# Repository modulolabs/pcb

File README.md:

Modulo PCBs
===

This repository contains modulo circuit board schematics and pcb layouts.

Repository Contents
---

* Base/ - Eagle files for the Modulo Base
* Controller/ - Eagle files for the Modulo Controller
* Display/ - Eagle files for the Modulo Display
* Eagle/ - Common eagle files and libraries
* IRRemote/ - Eagle files for the Modulo IR Transceiver
* Joystick/ - Eagle files for the Modulo Joystick
* Knob/ - Eagle files for the Modulo Knob
* MotorDriver/ - Eagle files for Modulo Motor Driver
* Panel/ - Scripts for combining individual eagle boards into panels
* ParticleBase/ - Eagle files for the Modulo Particle Base
* Programmer/ - Eagle files for a board that's used to program other modulo boards
* TempProbe/ - Eagle files for the Modulo Temp Probe

Export
---

To export data for manufacturing:

* Load and run Eagle/Modulo.cam from the eagle cam processor. This will generate files in <Board>/Modulo<Board>RFQ/
* Run the ulp moundsmd.ulp and save the mount files to the same RFQ directory
* Run Eagle/integer-bom.ulp to generate the bom file and save it to the same RFQ directory.

License Information
-------------------
These circuit board designs are release under  [Creative Commons ShareAlike 4.0 International](https://creativecommons.org/licenses/by-sa/4.0/).

Please use, reuse, and modify these files as you see fit. Please maintain attribute to Modulo Labs LLC and release derivative work under the same license.

Distributed as-is; no warranty is given.

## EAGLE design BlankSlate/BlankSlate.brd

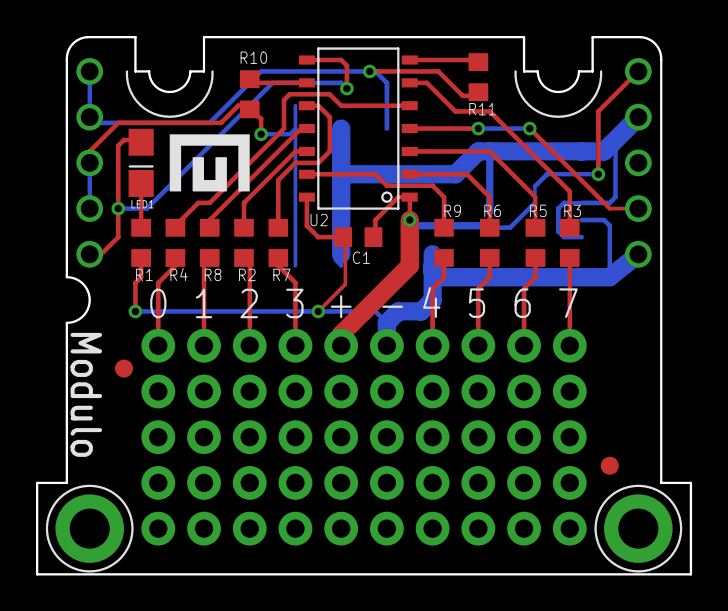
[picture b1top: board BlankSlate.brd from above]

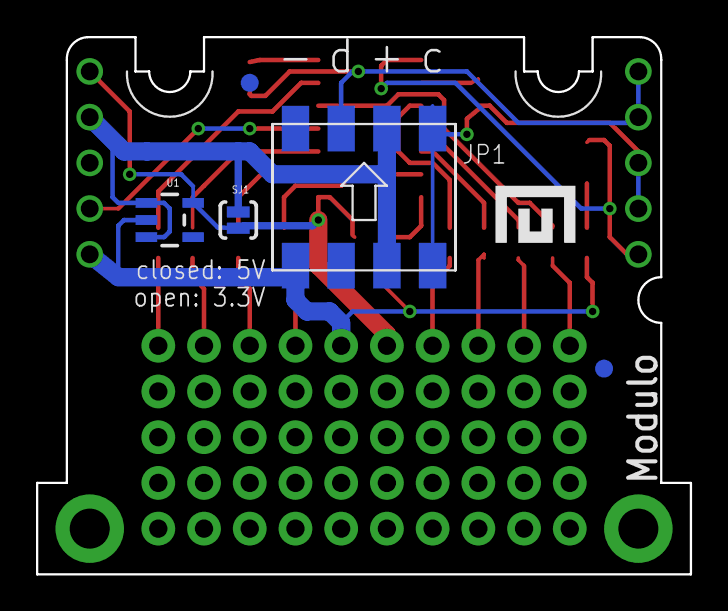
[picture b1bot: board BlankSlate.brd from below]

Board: 2 copper layers, 36.3 x 29.8 mm, 34 parts (16 on the bottom side), 26 nets.

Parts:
C1: .1uF; 0603
FID1, FID2, FID4, FID5: FIDUCIAL; FIDUCIAL_1MM
JP1: HEADER-1X4-AMPMODU; AMPMODU-4P
JP2, JP3, JP4, JP5, JP6, JP7, JP8, JP9, JP10, JP11: 1X05_NO_SILK
LED1: blue; 0805-LED
PCB1: DEVICE-PCB
R1: 1KΩ; 0603
R2, R3, R4, R5, R6, R7, R8, R9: 150Ω; 0603
R10, R11: 0Ω; 0603
SJ1: SOLDERJUMPERNO; SJ_2S-NO
U1: VREG-MIC5205-3.3V; SOT23-5
U2: ATTINY841; SOIC-14
U$1, U$2: LOGO-SMALL

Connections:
GND: C1.2, JP1.P$1, JP1.P$2, JP11.1, PCB1.GND, R1.1, U1.2, U2.14
IO0: R4.1, U2.5
IO1: R8.1, U2.11
IO2: R2.1, U2.12
IO3: R7.1, U2.10
IO4: R9.1, U2.13
IO5: R6.1, U2.2
IO6: R5.1, U2.3
IO7: R3.1, U2.6
MISO/LED: LED1.A, PCB1.MISO, U2.8
unnamed: JP4.1, R4.2
unnamed: JP5.1, R5.2
unnamed: JP7.1, R7.2
unnamed: JP2.1, R2.2
unnamed: JP3.1, R3.2
unnamed: JP6.1, R6.2
unnamed: JP9.1, R9.2
unnamed: LED1.C, R1.2
unnamed: JP8.1, R8.2
RESET: PCB1.RESET, U2.4
SCL: JP1.P$7, JP1.P$8, PCB1.CLK, PCB1.SCL, R10.1
SCL/SCK: R10.2, U2.9
SDA: JP1.P$3, JP1.P$4, PCB1.MOSI, PCB1.SDA, R11.1
SDA/MOSI: R11.2, U2.7
VCC: C1.1, JP10.1, PCB1.VPROG, SJ1.2, U1.5, U2.1
VIN: JP1.P$5, JP1.P$6, PCB1.VCC, SJ1.1, U1.1, U1.3

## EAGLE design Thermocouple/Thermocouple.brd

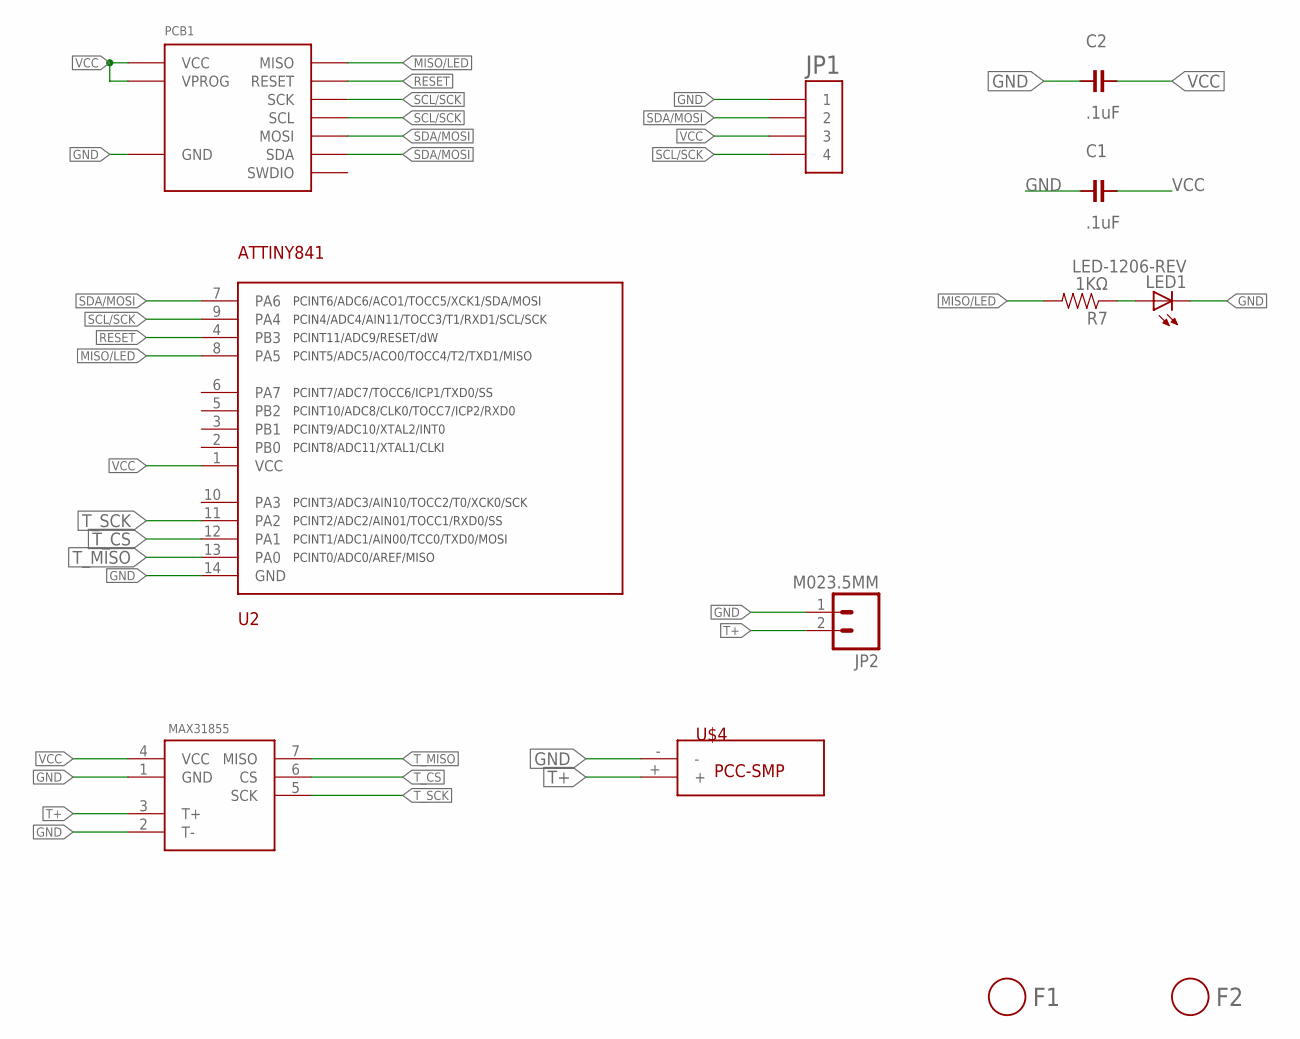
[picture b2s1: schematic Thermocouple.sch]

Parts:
C1, C2: .1uF; 0603
F1, F2: FIDUCIAL; FIDUCIAL_1MM
JP1: HEADER-1X4-AMPMODU; AMPMODU-4P
JP2: M023.5MM; SCREWTERMINAL-3.5MM-2
LED1: LED-1206-REV
PCB1: DEVICE-PCB; PARTNUM Therm PCB
R7: 1KΩ; 0603
U2: ATTINY841; SOIC-14
U$4: PCC-SMP
U$5: MAX31855; SOIC-8

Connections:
GND: C1.2, C2.2, JP1.P$1 (1), JP1.P$2 (1), JP2.1, LED1.C, PCB1.GND, U2.14 (GND), U$4.-, U$5.1 (GND), U$5.2 (T-)
MISO/LED: PCB1.MISO, R7.2, U2.8 (PA5)
unnamed: LED1.A, R7.1
RESET: PCB1.RESET, U2.4 (PB3)
SCL/SCK: JP1.P$7 (4), JP1.P$8 (4), PCB1.CLK (SCK), PCB1.SCL, U2.9 (PA4)
SDA/MOSI: JP1.P$3 (2), JP1.P$4 (2), PCB1.MOSI, PCB1.SDA, U2.7 (PA6)
T+: JP2.2, U$4.+, U$5.3 (T+)
T_CS: U2.12 (PA1), U$5.6 (CS)
T_MISO: U2.13 (PA0), U$5.7 (MISO)
T_SCK: U2.11 (PA2), U$5.5 (SCK)
VCC: C1.1, C2.1, JP1.P$5 (3), JP1.P$6 (3), PCB1.VCC, PCB1.VPROG, U2.1 (VCC), U$5.4 (VCC)

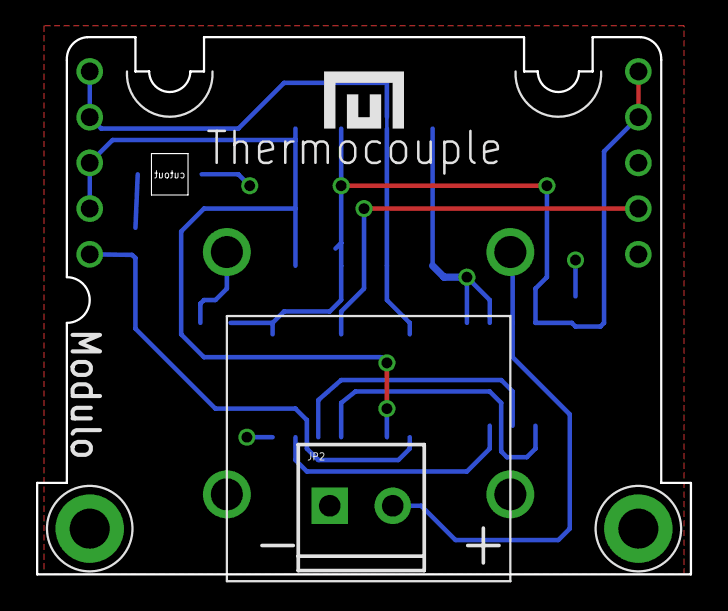
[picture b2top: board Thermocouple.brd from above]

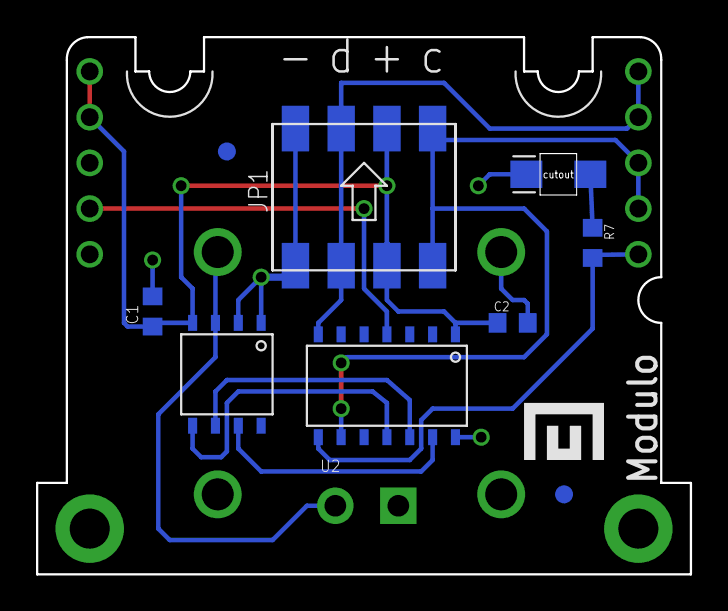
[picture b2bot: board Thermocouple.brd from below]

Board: 2 copper layers, 36.3 x 29.8 mm, 14 parts (10 on the bottom side), 11 nets.

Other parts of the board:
U$2, U$3: LOGO-SMALL

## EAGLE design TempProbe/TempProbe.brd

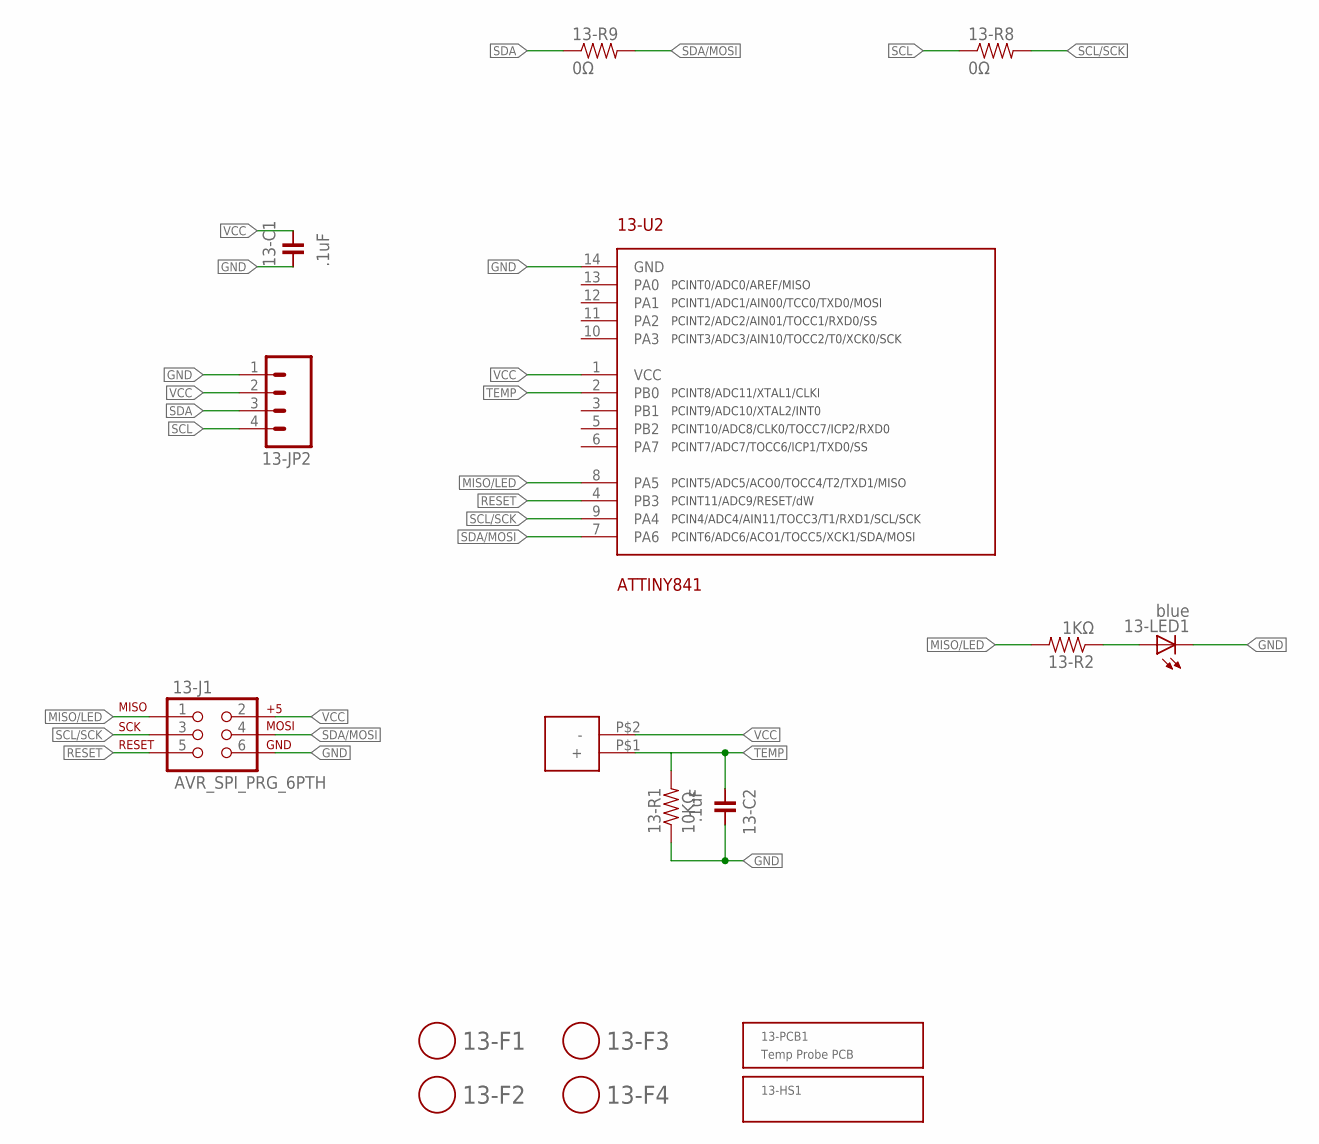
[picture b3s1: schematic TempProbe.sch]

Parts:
13-C1, 13-C2: .1uF; 0603
13-F1, 13-F2, 13-F3, 13-F4: FIDUCIAL; FIDUCIAL_1MM
13-J1: AVR_SPI_PRG_6PTH; 2X3
13-JP2: M041X04_NO_SILK; 1X04_NO_SILK
13-LED1: blue; 0805-LED
13-PROBE1: TEMP-PROBE; TEMP_PROBE; PARTNUM NTCLE413E2103F102L
13-R1: 10KΩ; 0603
13-R2: 1KΩ; 0603
13-R8, 13-R9: 0Ω; 0603
13-U2: ATTINY841; SOIC-14

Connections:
GND: 13-C1.2, 13-C2.1, 13-J1.6, 13-JP2.1, 13-LED1.C, 13-R1.1, 13-U2.14 (GND)
MISO/LED: 13-J1.1, 13-R2.2, 13-U2.8 (PA5)
unnamed: 13-LED1.A, 13-R2.1
RESET: 13-J1.5, 13-U2.4 (PB3)
SCL: 13-JP2.4, 13-R8.1
SCL/SCK: 13-J1.3, 13-R8.2, 13-U2.9 (PA4)
SDA: 13-JP2.3, 13-R9.1
SDA/MOSI: 13-J1.4, 13-R9.2, 13-U2.7 (PA6)
TEMP: 13-C2.2, 13-PROBE1.P$1 (+), 13-R1.2, 13-U2.2 (PB0)
VCC: 13-C1.1, 13-J1.2, 13-JP2.2, 13-PROBE1.P$2 (-), 13-U2.1 (VCC)

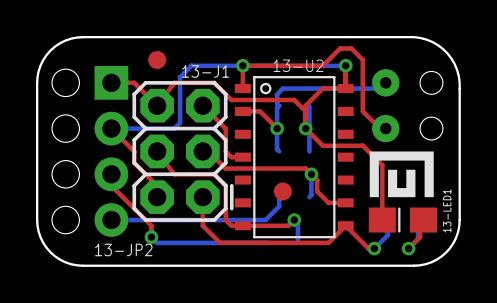
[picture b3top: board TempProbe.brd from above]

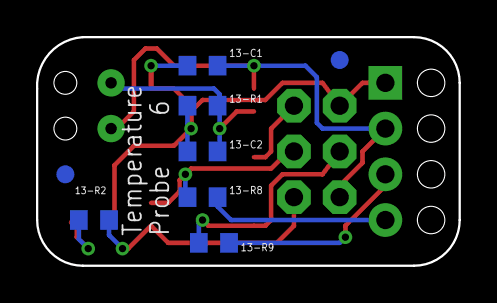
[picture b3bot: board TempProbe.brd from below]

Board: 2 copper layers, 23.5 x 12.7 mm, 16 parts (8 on the bottom side), 10 nets.

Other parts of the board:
U$1: LOGO-TINY

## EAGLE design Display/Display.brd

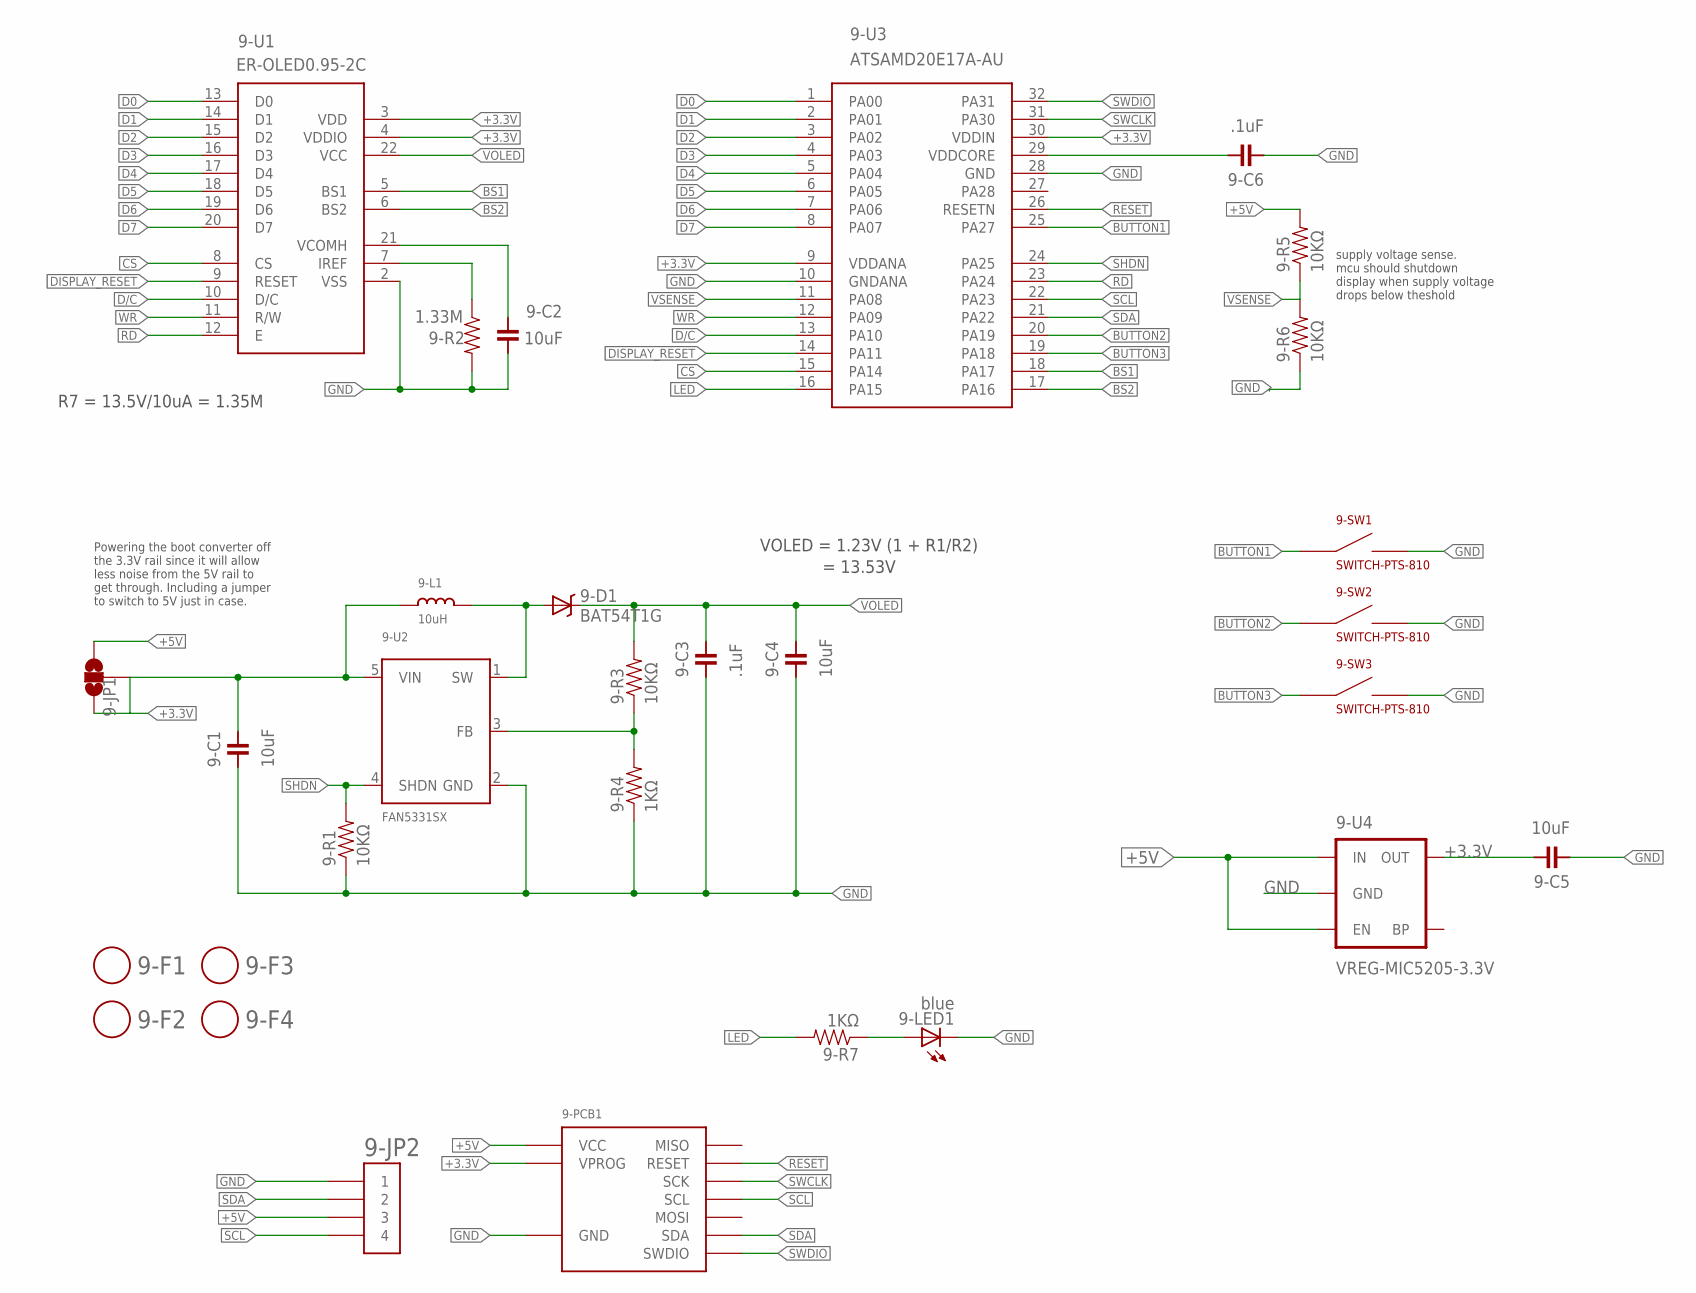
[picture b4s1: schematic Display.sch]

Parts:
9-C1, 9-C2, 9-C4, 9-C5: 10uF; 0603
9-C3, 9-C6: .1uF; 0603
9-D1: BAT54T1G; SMP
9-F1, 9-F2, 9-F3, 9-F4: FIDUCIAL; FIDUCIAL_1MM
9-JP1: SOLDERJUMPER_2WAYS; SJ_3
9-JP2: HEADER-1X4-AMPMODU; AMPMODU-4P
9-L1: 10uH; INDUCTOR_1007; PARTNUM MPI2520R1-100-R
9-LED1: blue; 0805-LED
9-PCB1: DEVICE-PCB; PARTNUM Display PCB
9-R1, 9-R3, 9-R5, 9-R6: 10KΩ; 0603
9-R2: 1.33M; 0603; PARTNUM ERJ-3EKF1304V
9-R4, 9-R7: 1KΩ; 0603
9-SW1, 9-SW2, 9-SW3: SWITCH-PTS-810; TACT-SWITCH-PTS-810
9-U1: ER-OLED0.95-2C; FPC-24-REVERSE; PARTNUM ER-OLED0.95-2C
9-U2: FAN5331SX; SOT23-5; PARTNUM FAN5331SX
9-U3: ATSAMD20E17A-AU; TQFP-32; PARTNUM ATSAMD20E17A-AU
9-U4: VREG-MIC5205-3.3V; SOT23-5; PARTNUM MIC5205-3.3YM5 TR

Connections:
+3.3V: 9-C1.1, 9-C5.1, 9-JP1.1, 9-JP1.2, 9-L1.P$1 (1), 9-PCB1.VPROG, 9-U1.3 (VDD), 9-U1.4 (VDDIO), 9-U2.5 (VIN), 9-U3.9 (VDDANA), 9-U3.30 (VDDIN), 9-U4.5 (OUT)
+5V: 9-JP1.3, 9-JP2.P$5 (3), 9-JP2.P$6 (3), 9-PCB1.VCC, 9-R5.2, 9-U4.1 (IN), 9-U4.3 (EN)
BS1: 9-U1.5 (BS1), 9-U3.18 (PA17)
BS2: 9-U1.6 (BS2), 9-U3.17 (PA16)
BUTTON1: 9-SW1.P$1 (POS1), 9-SW1.P$2 (POS1), 9-U3.25 (PA27)
BUTTON2: 9-SW2.P$1 (POS1), 9-SW2.P$2 (POS1), 9-U3.20 (PA19)
BUTTON3: 9-SW3.P$1 (POS1), 9-SW3.P$2 (POS1), 9-U3.19 (PA18)
CS: 9-U1.8 (CS), 9-U3.15 (PA14)
D0: 9-U1.13 (D0), 9-U3.1 (PA00)
D1: 9-U1.14 (D1), 9-U3.2 (PA01)
D2: 9-U1.15 (D2), 9-U3.3 (PA02)
D3: 9-U1.16 (D3), 9-U3.4 (PA03)
D4: 9-U1.17 (D4), 9-U3.5 (PA04)
D5: 9-U1.18 (D5), 9-U3.6 (PA05)
D6: 9-U1.19 (D6), 9-U3.7 (PA06)
D7: 9-U1.20 (D7), 9-U3.8 (PA07)
D/C: 9-U1.10 (D/C), 9-U3.13 (PA10)
DISPLAY_RESET: 9-U1.9 (RESET), 9-U3.14 (PA11)
GND: 9-C1.2, 9-C2.2, 9-C3.2, 9-C4.2, 9-C5.2, 9-C6.2, 9-JP2.P$1 (1), 9-JP2.P$2 (1), 9-LED1.C, 9-PCB1.GND, 9-R1.1, 9-R2.2, 9-R4.1, 9-R6.1, 9-SW1.P$3 (NEG1), 9-SW1.P$4 (NEG1), 9-SW2.P$3 (NEG1), 9-SW2.P$4 (NEG1), 9-SW3.P$3 (NEG1), 9-SW3.P$4 (NEG1), 9-U1.2 (VSS), 9-U2.2 (GND), 9-U3.10 (GNDANA), 9-U3.28 (GND), 9-U4.2 (GND)
LED: 9-R7.2, 9-U3.16 (PA15)
unnamed: 9-D1.A, 9-L1.P$2 (2), 9-U2.1 (SW)
unnamed: 9-R3.1, 9-R4.2, 9-U2.3 (FB)
unnamed: 9-C6.1, 9-U3.29 (VDDCORE)
unnamed: 9-C2.1, 9-U1.21 (VCOMH)
unnamed: 9-LED1.A, 9-R7.1
unnamed: 9-R2.1, 9-U1.7 (IREF)
RD: 9-U1.12 (E), 9-U3.23 (PA24)
RESET: 9-PCB1.RESET, 9-U3.26 (RESETN)
SCL: 9-JP2.P$7 (4), 9-JP2.P$8 (4), 9-PCB1.SCL, 9-U3.22 (PA23)
SDA: 9-JP2.P$3 (2), 9-JP2.P$4 (2), 9-PCB1.SDA, 9-U3.21 (PA22)
SHDN: 9-R1.2, 9-U2.4 (SHDN), 9-U3.24 (PA25)
SWCLK: 9-PCB1.CLK (SCK), 9-U3.31 (PA30)
SWDIO: 9-PCB1.SWDIO, 9-U3.32 (PA31)
VOLED: 9-C3.1, 9-C4.1, 9-D1.C, 9-R3.2, 9-U1.22 (VCC)
VSENSE: 9-R5.1, 9-R6.2, 9-U3.11 (PA08)
WR: 9-U1.11 (R/W), 9-U3.12 (PA09)

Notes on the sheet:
VOLED = 1.23V (1 + R1/R2)
= 13.53V
R7 = 13.5V/10uA = 1.35M
supply voltage sense. mcu should shutdown display when supply voltage drops below theshold
Powering the boot converter off the 3.3V rail since it will allow less noise from the 5V rail to get through. Including a jumper to switch to 5V just in case.

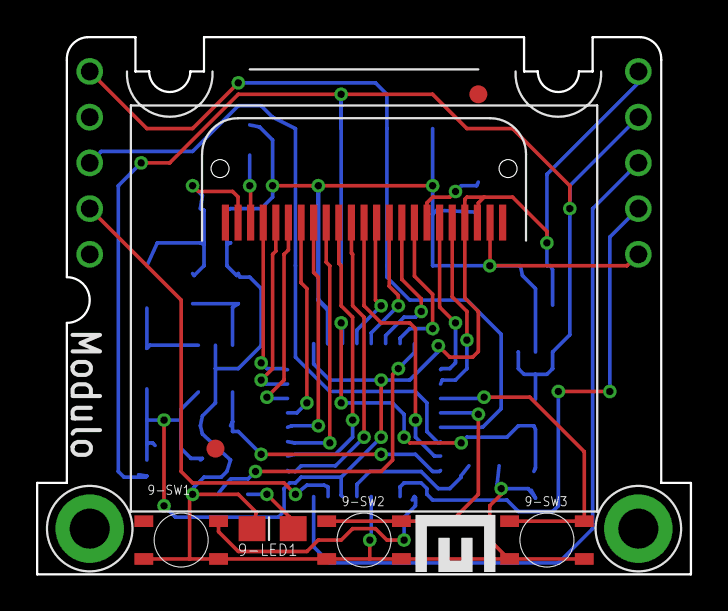
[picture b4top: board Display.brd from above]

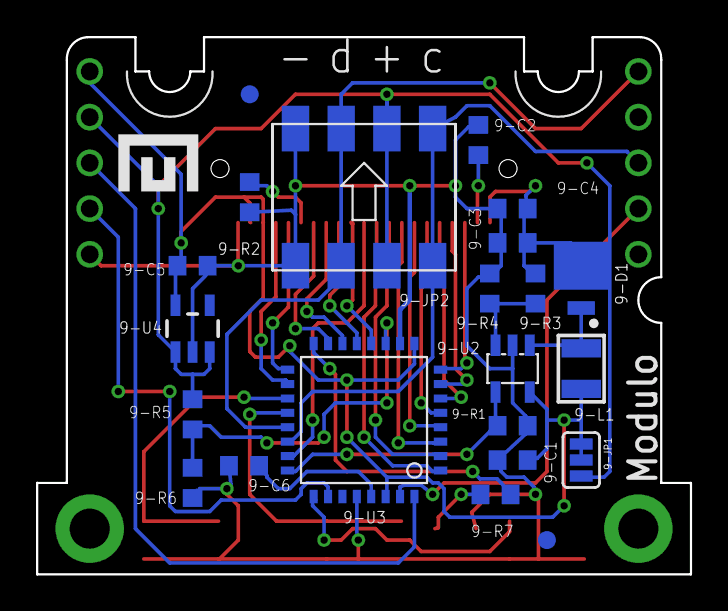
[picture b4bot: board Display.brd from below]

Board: 2 copper layers, 36.3 x 29.8 mm, 32 parts (23 on the bottom side), 36 nets.

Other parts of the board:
U$1, U$2: LOGO-SMALL

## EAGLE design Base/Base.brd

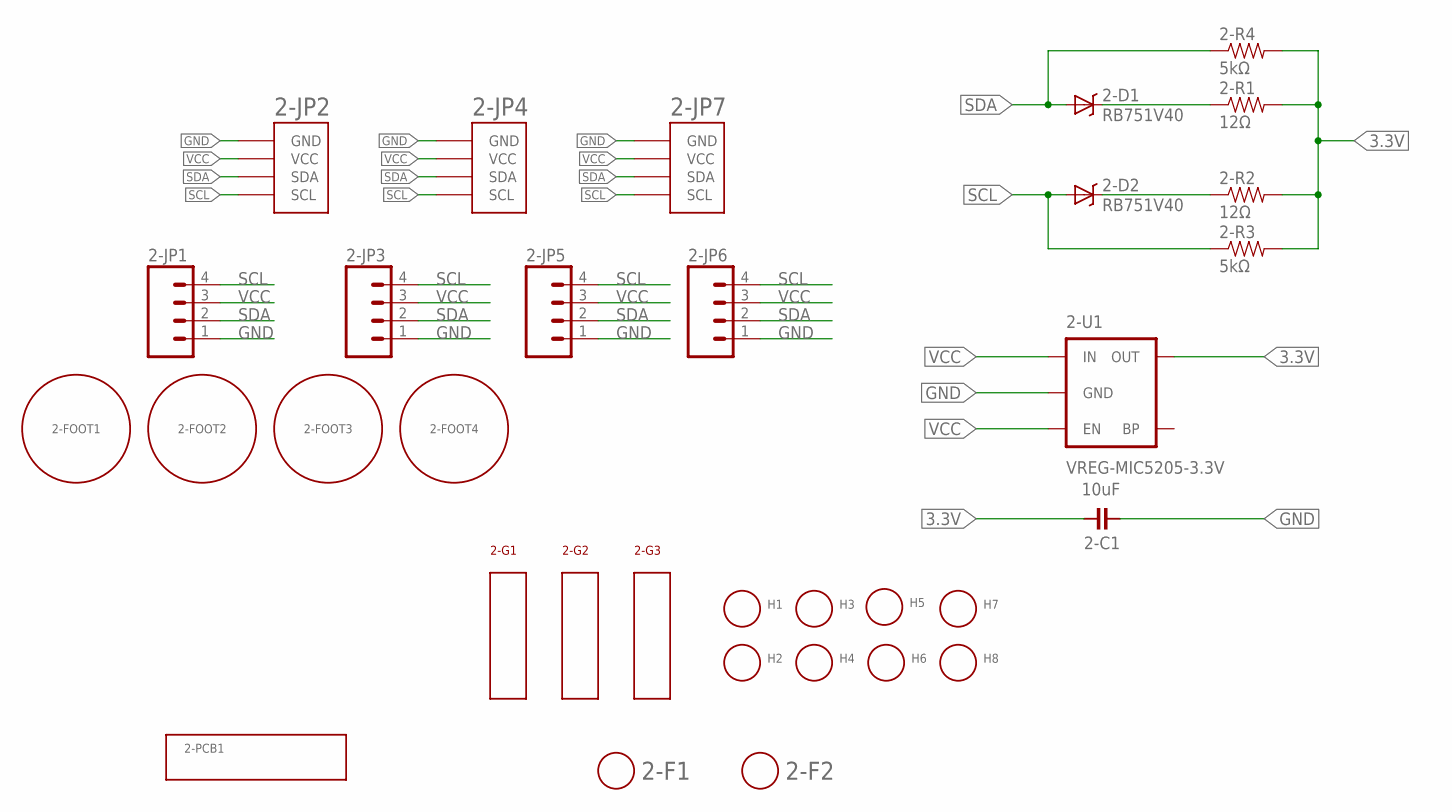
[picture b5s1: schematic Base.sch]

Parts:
2-C1: 10uF; 0603
2-D1, 2-D2: RB751V40; SOD-323; PARTNUM RB751V40
2-F1, 2-F2: FIDUCIAL; FIDUCIAL_1MM
2-FOOT1, 2-FOOT2, 2-FOOT3, 2-FOOT4: FOOT
2-G1, 2-G3: CARD-GUIDE; CARD-GUIDE-2; PARTNUM HCG-201-165
2-G2: CARD-GUIDE; CARD-GUIDE-2; PARTNUM HCG-202-165
2-JP1, 2-JP3, 2-JP5, 2-JP6: M04LOCK; 1X04_LOCK; PARTNUM M20-9750446
2-JP2, 2-JP4, 2-JP7: HEADER-MODULO; JST-PA-SIDE-SMD
2-R1, 2-R2: 12Ω; 0603
2-R3, 2-R4: 5kΩ; 0603
2-U1: VREG-MIC5205-3.3V; SOT23-5
H1, H2, H3, H4, H5, H6, H7, H8: HOLE#2; HOLE-#2

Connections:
3.3V: 2-C1.1, 2-R1.2, 2-R2.2, 2-R3.2, 2-R4.2, 2-U1.5 (OUT)
GND: 2-C1.2, 2-JP1.1, 2-JP2.1 (GND), 2-JP3.1, 2-JP4.1 (GND), 2-JP5.1, 2-JP6.1, 2-JP7.1 (GND), 2-U1.2 (GND)
unnamed: 2-D2.C, 2-R2.1
unnamed: 2-D1.C, 2-R1.1
SCL: 2-D2.A, 2-JP1.4, 2-JP2.4 (SCL), 2-JP3.4, 2-JP4.4 (SCL), 2-JP5.4, 2-JP6.4, 2-JP7.4 (SCL), 2-R3.1
SDA: 2-D1.A, 2-JP1.2, 2-JP2.3 (SDA), 2-JP3.2, 2-JP4.3 (SDA), 2-JP5.2, 2-JP6.2, 2-JP7.3 (SDA), 2-R4.1
VCC: 2-JP1.3, 2-JP2.2 (VCC), 2-JP3.3, 2-JP4.2 (VCC), 2-JP5.3, 2-JP6.3, 2-JP7.2 (VCC), 2-U1.1 (IN), 2-U1.3 (EN)

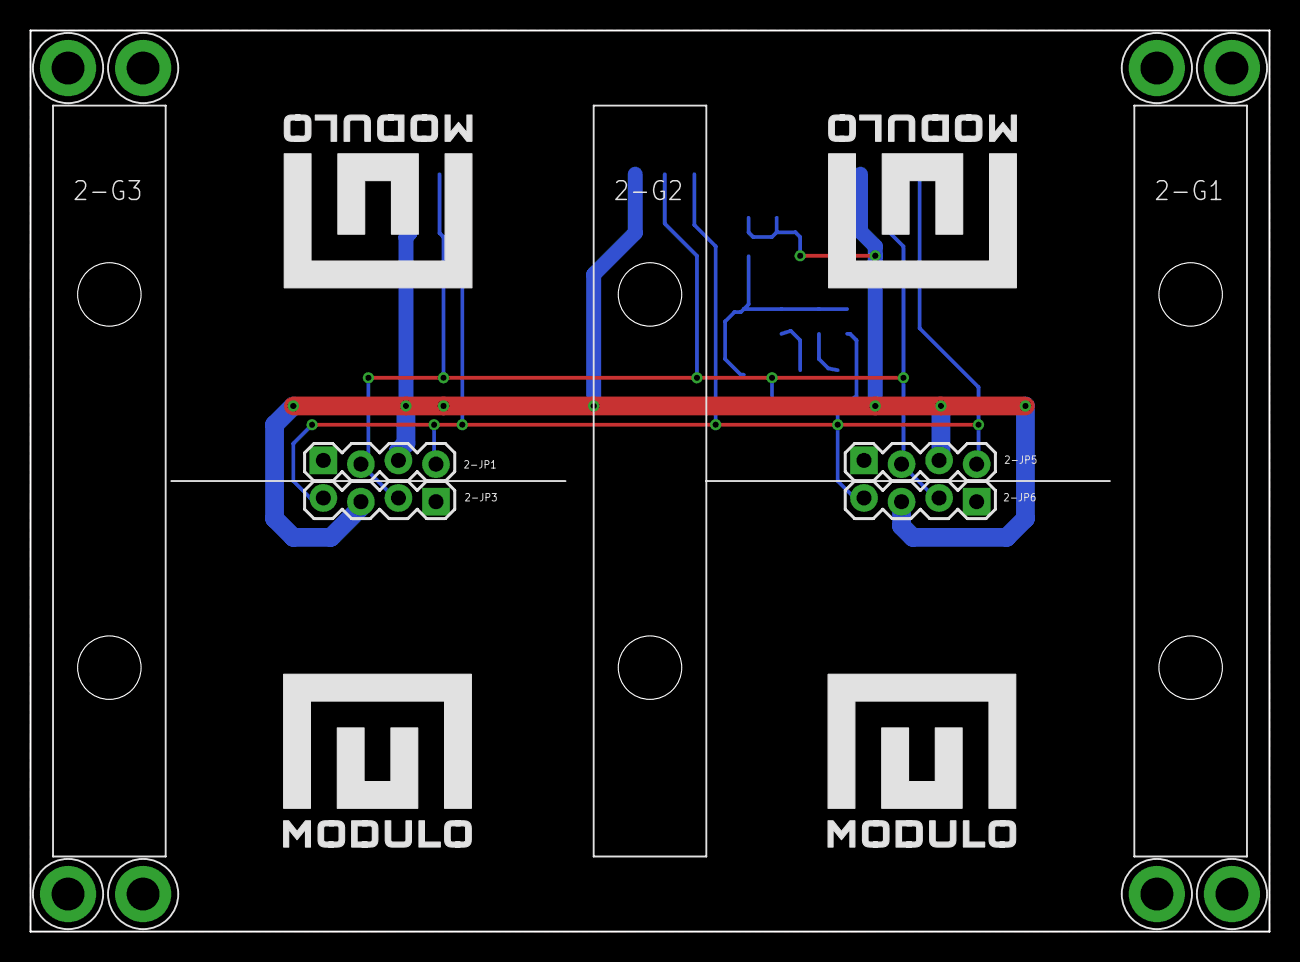
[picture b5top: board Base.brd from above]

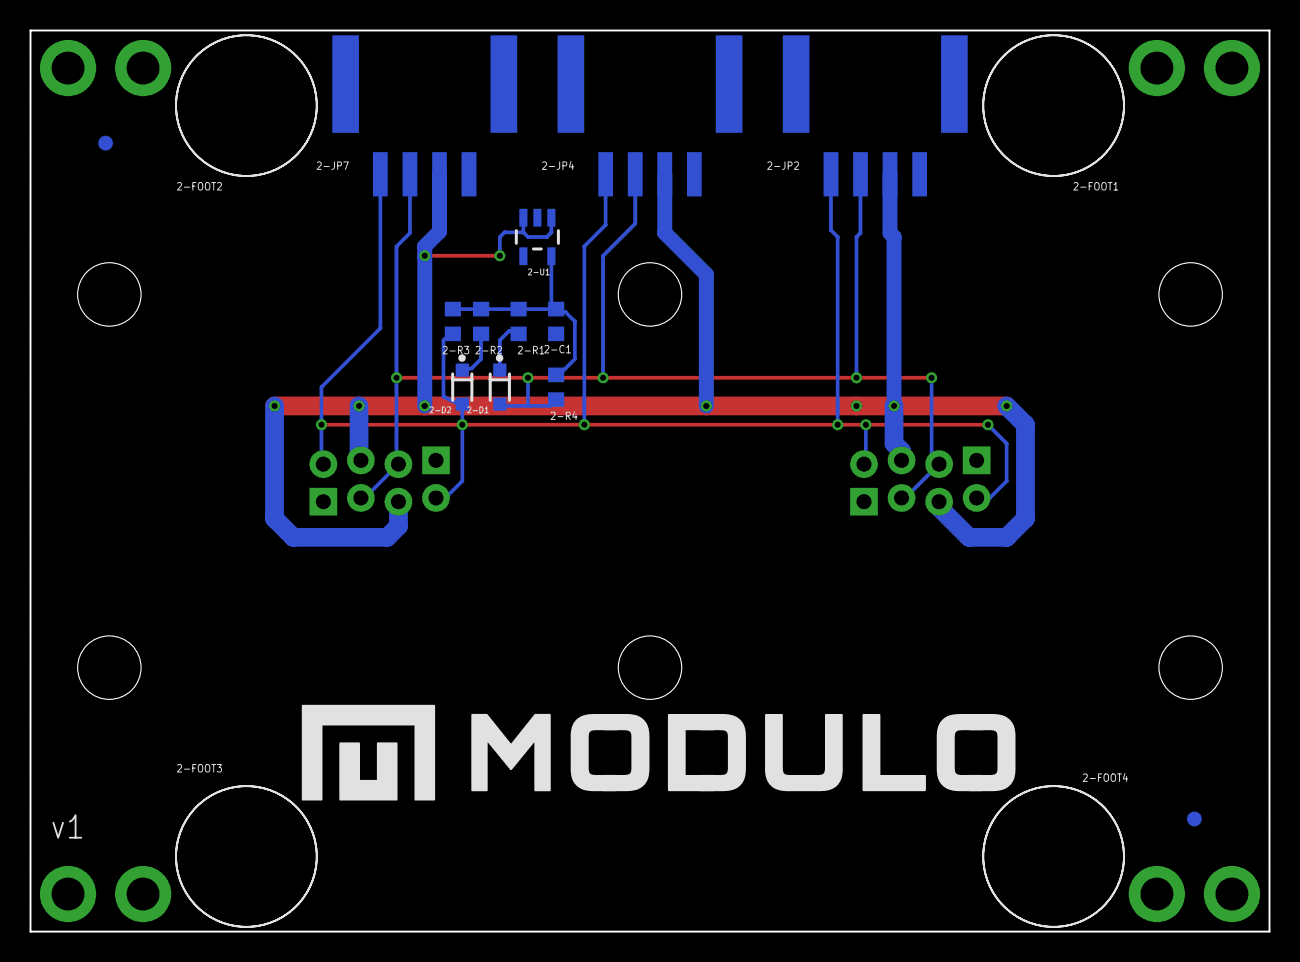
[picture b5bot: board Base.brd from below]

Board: 2 copper layers, 83.8 x 61.0 mm, 37 parts (18 on the bottom side), 7 nets.

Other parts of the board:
U$1: LOGO-HOR-0.25
U$3, U$4, U$5, U$6: LOGO-0.5

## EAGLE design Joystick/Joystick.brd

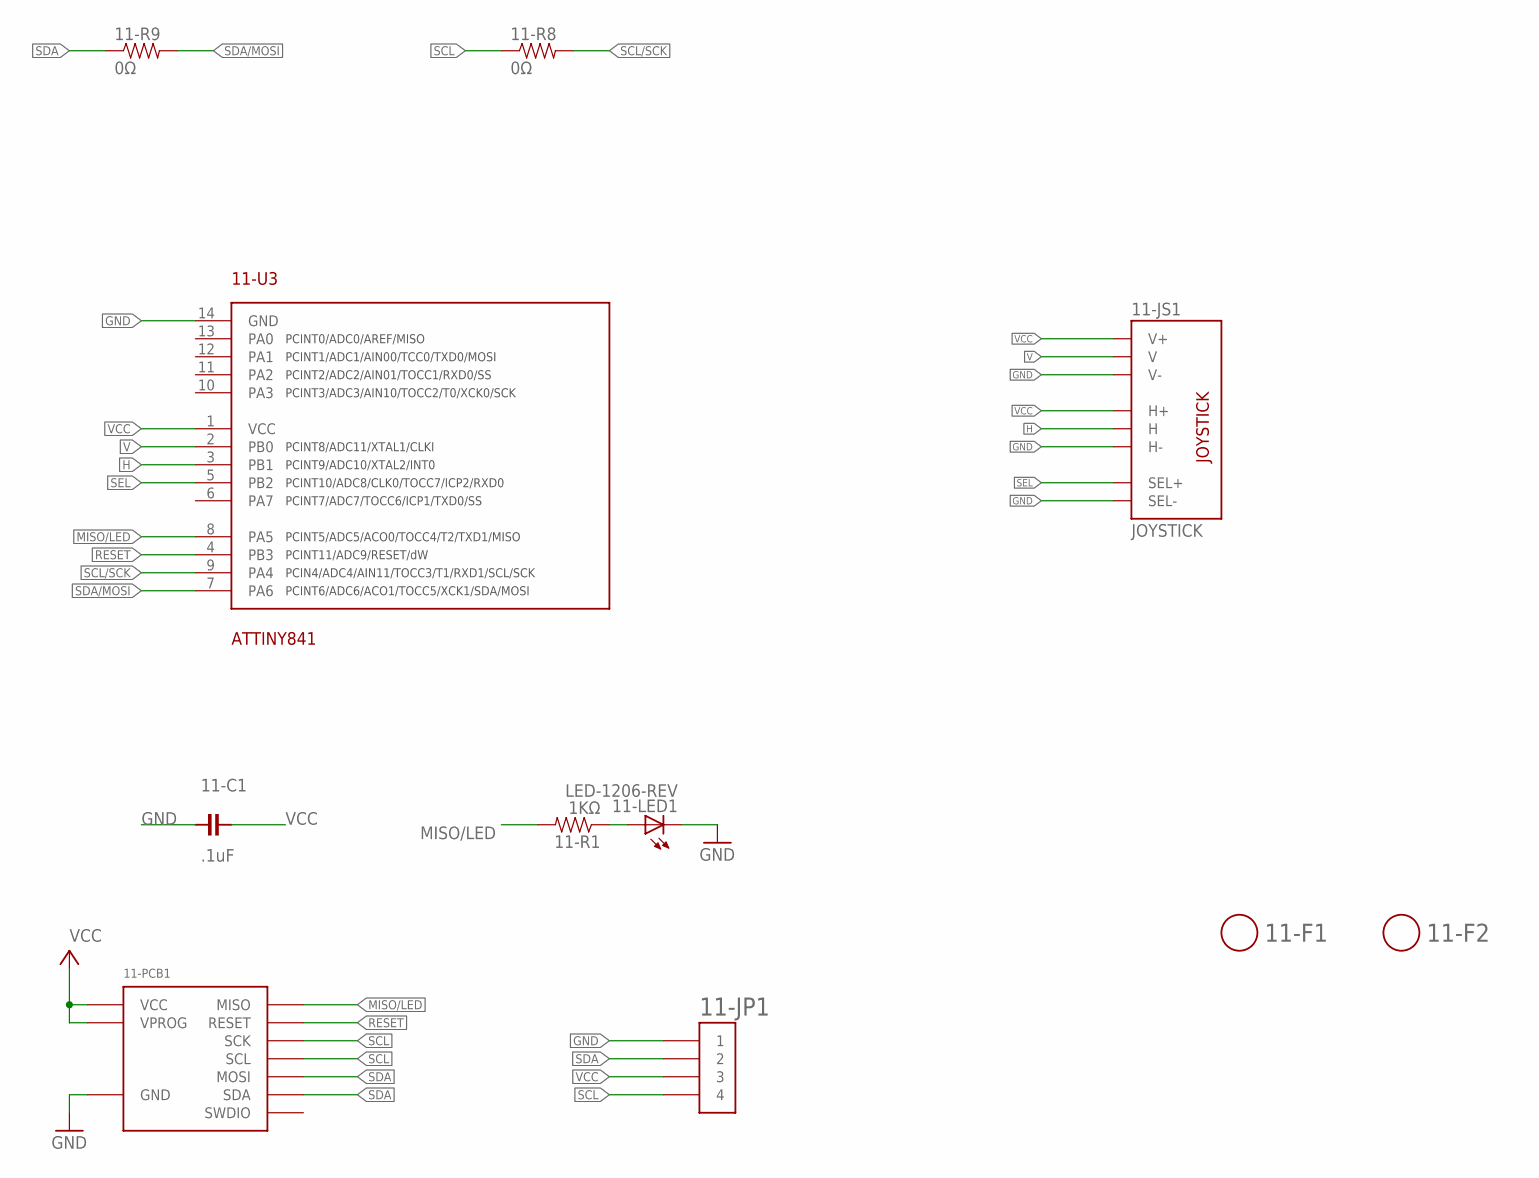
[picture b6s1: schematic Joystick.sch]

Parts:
11-C1: .1uF; 0603
11-F1, 11-F2: FIDUCIAL; FIDUCIAL_1MM
11-JP1: HEADER-1X4-AMPMODU; AMPMODU-4P
11-JS1: JOYSTICK; PARTNUM Joystick
11-LED1: LED-1206-REV
11-PCB1: DEVICE-PCB; PARTNUM Joystick PCB
11-R1: 1KΩ; 0603
11-R8, 11-R9: 0Ω; 0603
11-U3: ATTINY841; SOIC-14

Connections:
GND: 11-C1.2, 11-JP1.P$1 (1), 11-JP1.P$2 (1), 11-JS1.B2A (SEL-), 11-JS1.H3 (H-), 11-JS1.V3 (V-), 11-LED1.C, 11-PCB1.GND, 11-U3.14 (GND)
H: 11-JS1.H2 (H), 11-U3.3 (PB1)
MISO/LED: 11-PCB1.MISO, 11-R1.2, 11-U3.8 (PA5)
unnamed: 11-LED1.A, 11-R1.1
RESET: 11-PCB1.RESET, 11-U3.4 (PB3)
SCL: 11-JP1.P$7 (4), 11-JP1.P$8 (4), 11-PCB1.CLK (SCK), 11-PCB1.SCL, 11-R8.1
SCL/SCK: 11-R8.2, 11-U3.9 (PA4)
SDA: 11-JP1.P$3 (2), 11-JP1.P$4 (2), 11-PCB1.MOSI, 11-PCB1.SDA, 11-R9.1
SDA/MOSI: 11-R9.2, 11-U3.7 (PA6)
SEL: 11-JS1.B1A (SEL+), 11-U3.5 (PB2)
V: 11-JS1.V2 (V), 11-U3.2 (PB0)
VCC: 11-C1.1, 11-JP1.P$5 (3), 11-JP1.P$6 (3), 11-JS1.H1 (H+), 11-JS1.V1 (V+), 11-PCB1.VCC, 11-PCB1.VPROG, 11-U3.1 (VCC)

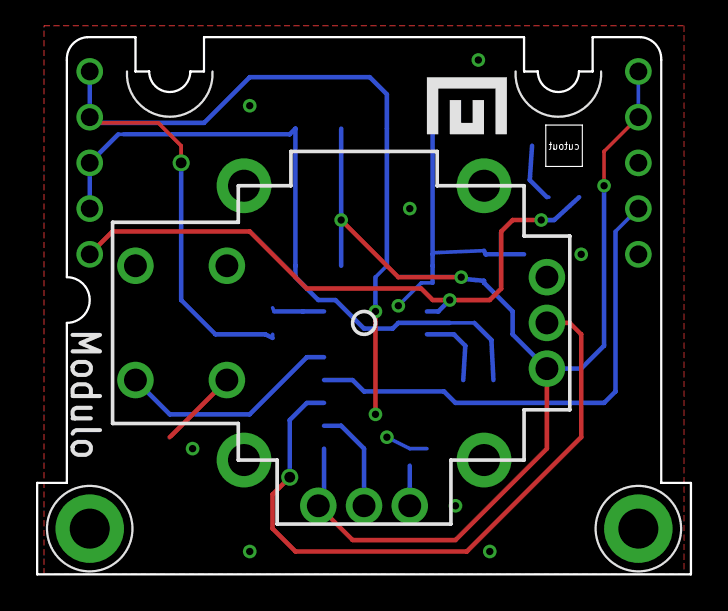
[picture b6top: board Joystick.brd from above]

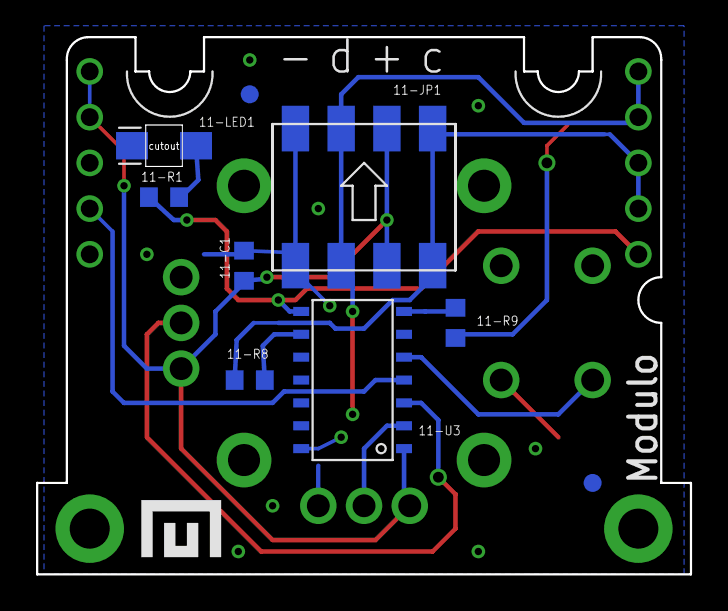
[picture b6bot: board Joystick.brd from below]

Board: 2 copper layers, 36.3 x 29.8 mm, 13 parts (10 on the bottom side), 12 nets.

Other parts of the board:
U$1, U$2: LOGO-SMALL

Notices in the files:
parts and their libraries:
SparkFun-Connectors: Licensing: Creative Commons ShareAlike 4.0 International - https://creativecommons.org/licenses/by-sa/4.0
